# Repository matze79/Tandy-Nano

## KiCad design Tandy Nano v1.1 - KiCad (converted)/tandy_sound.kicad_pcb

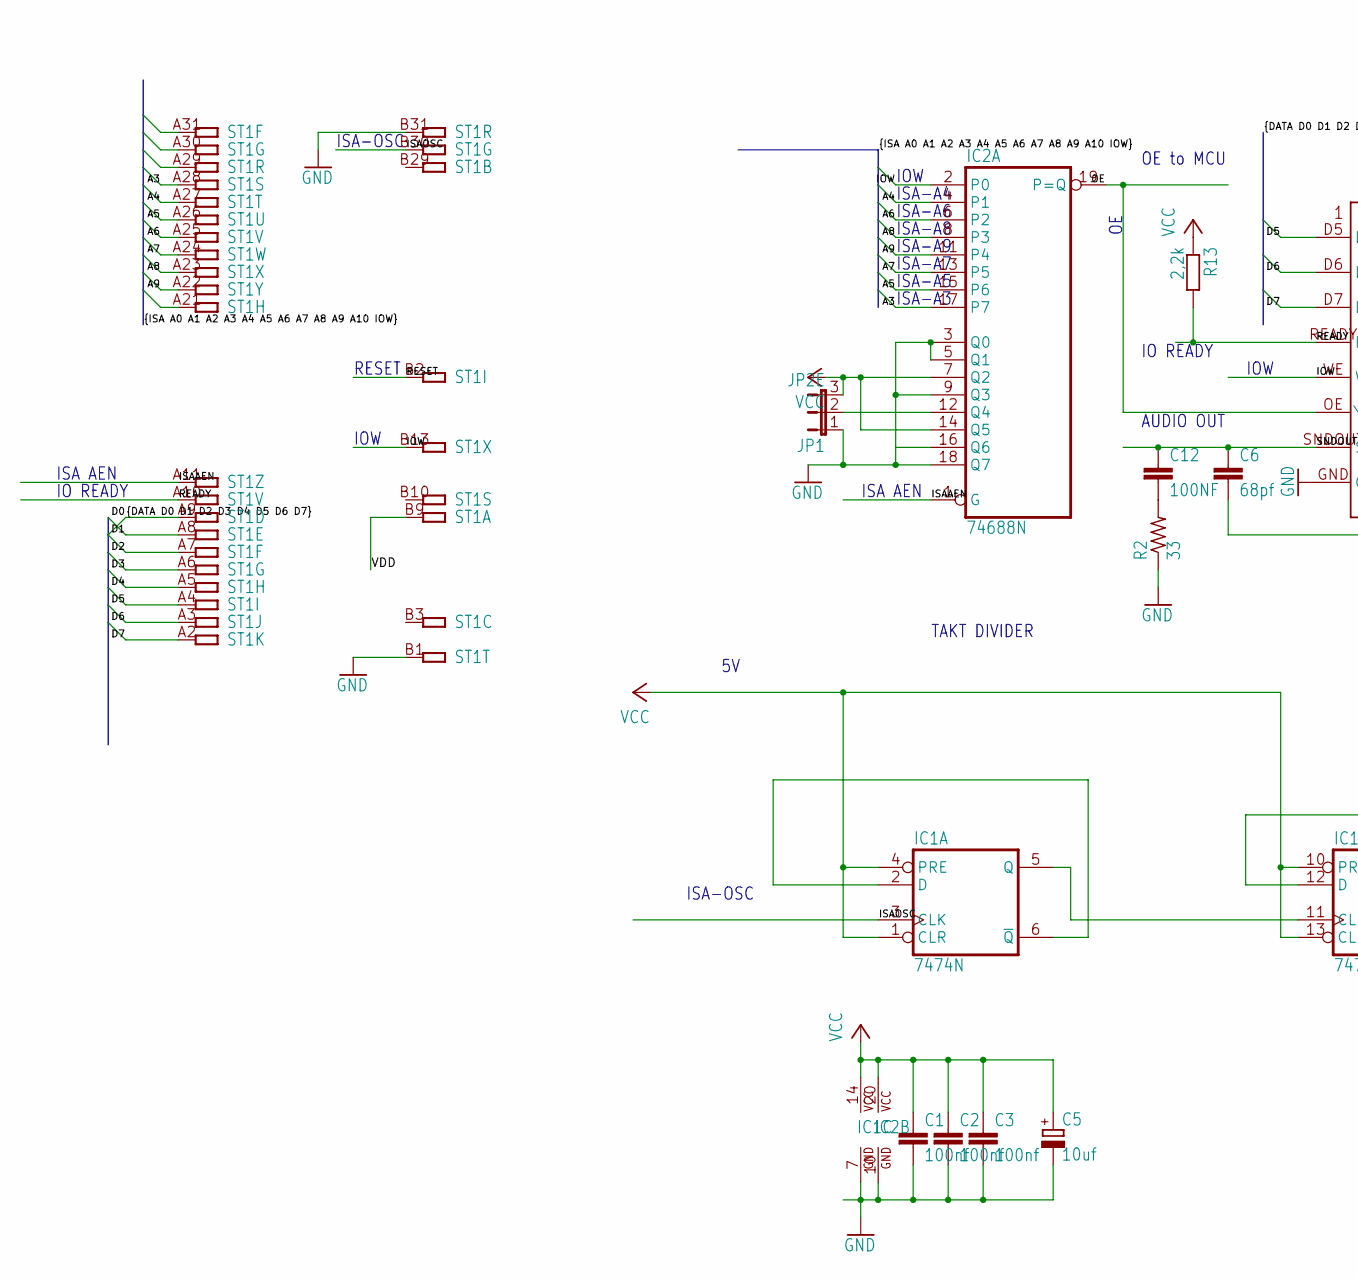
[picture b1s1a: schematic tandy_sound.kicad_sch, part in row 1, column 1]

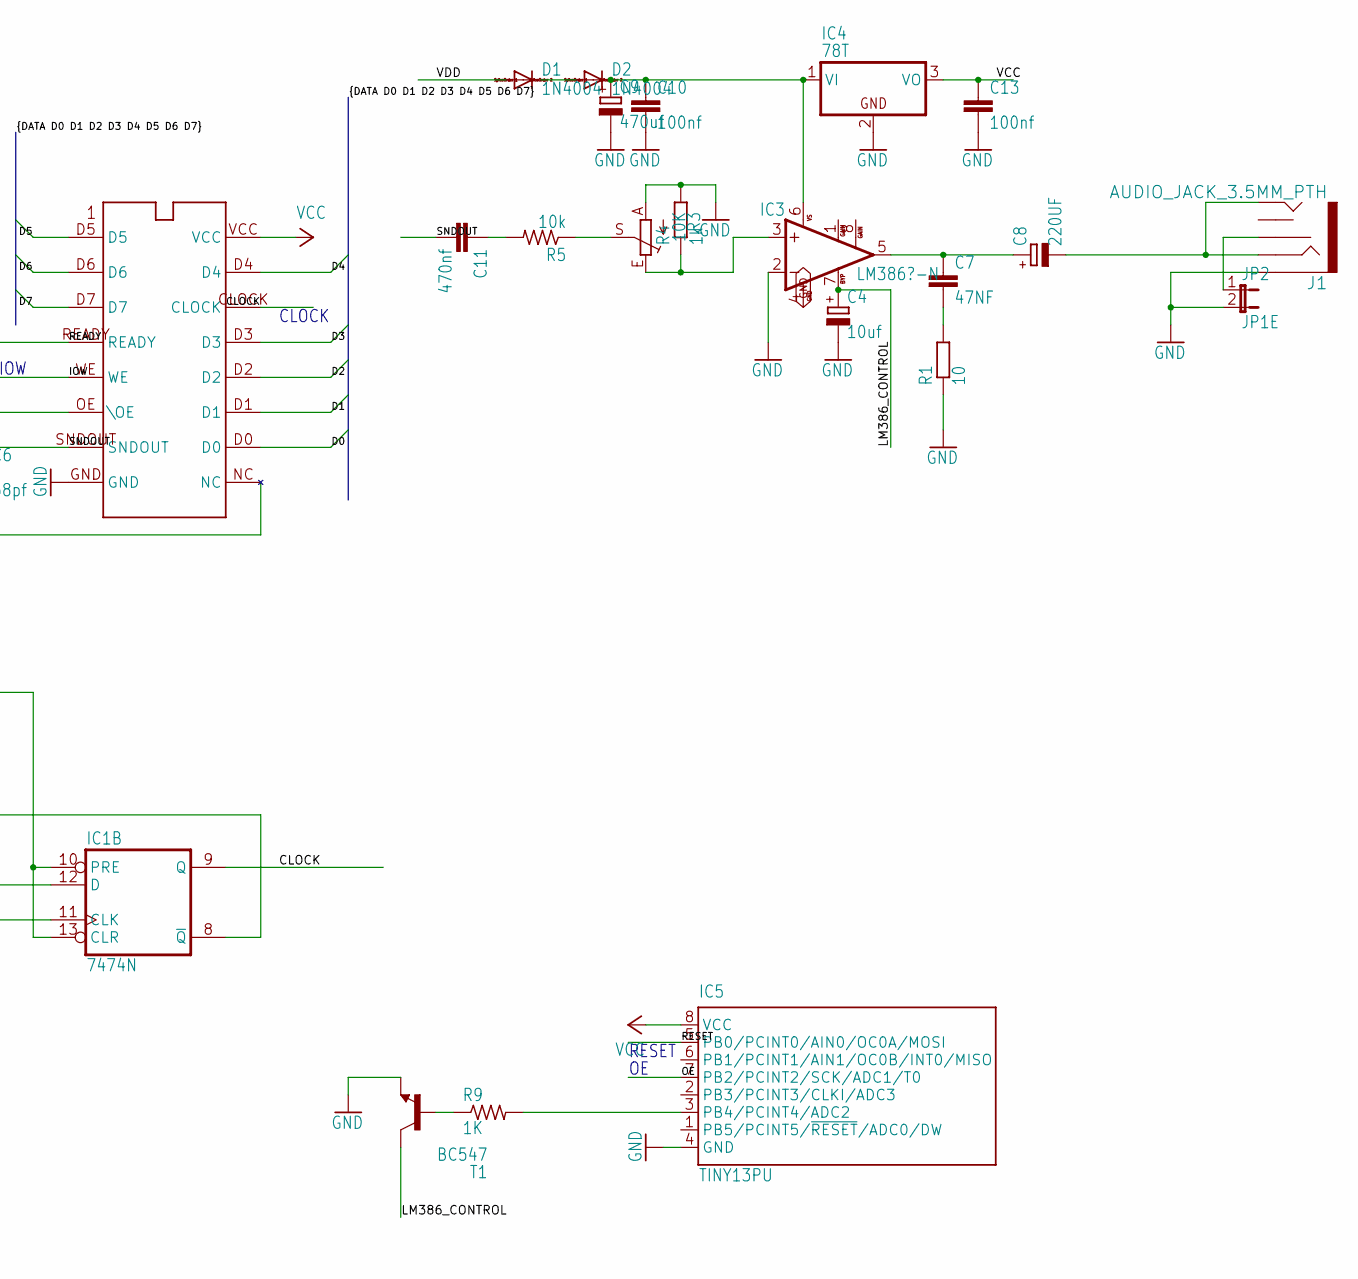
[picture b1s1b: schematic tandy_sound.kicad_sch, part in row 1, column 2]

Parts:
C1, C2, C3, C10, C13: 100nf; C2.5-3
C4, C5: 10uf; E2,5-6
C6: 68pf; C025-030X050
C7: 47NF; C025-030X050
C8: 220UF; E2,5-6E
C9: 470uf; E2,5-6
C11: 470nf; C025-030X050
C12: 100NF; C025-030X050
D1, D2: 1N4004; DO41-10
IC1: 7474N; DIL14
IC2: 74688N; DIL20
IC3: LM386?-N; DIL08
IC4: 78T; TO220H
IC5: TINY13PU; DIL08
J1: AUDIO_JACK_3.5MM_PTH; AUDIO-JACK
JP1: JP2E; JP2
JP2: JP1E; JP1
R1: 10; 0207_10
R2: 33; 0204V
R3: 10K; PT-10S
R4: 1k; 0207_10
R5: 10k; 0204V
R9: 1K; 0204V
R13: 2,2k; 0207_10
ST1: IBM8BIT
T1: BC547; TO92
U$1: SN76489; DIL16

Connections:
A0: ST1.A31
A1: ST1.A30
A2: ST1.A29
A3: IC2.17 (P7), ST1.A28
A4: IC2.4 (P1), ST1.A27
A5: IC2.15 (P6), ST1.A26
A6: IC2.6 (P2), ST1.A25
A7: IC2.13 (P5), ST1.A24
A8: IC2.8 (P3), ST1.A23
A9: IC2.11 (P4), ST1.A22
A10: ST1.A21
CLOCK: IC1.9 (Q), U$1.CLOCK
CMS_CLOCK: IC1.5 (Q), IC1.11 (CLK)
D0: ST1.A9, U$1.D0
D1: ST1.A8, U$1.D1
D2: ST1.A7, U$1.D2
D3: ST1.A6, U$1.D3
D4: ST1.A5, U$1.D4
D5: ST1.A4, U$1.D5
D6: ST1.A3, U$1.D6
D7: ST1.A2, U$1.D7
GND: C1.2, C2.2, C3.2, C4.-, C5.-, C9.-, C10.2, C13.2, IC1.7 (GND), IC2.3 (Q0), IC2.5 (Q1), IC2.9 (Q3), IC2.10 (GND), IC2.16 (Q6), IC2.18 (Q7), IC3.2 (-IN), IC3.4 (GND), IC4.2 (GND), IC5.4 (GND), J1.SLEEVE, JP1.1, JP2.2, R1.1, R2.1, R3.A, R4.2, ST1.B1, ST1.B31, T1.1 (E), U$1.GND
IOW: IC2.2 (P0), ST1.B13, U$1.WE
ISAAEN: IC2.1 (G), ST1.A11
ISAOSC: IC1.3 (CLK), ST1.B30
LM386_CONTROL: C4.+, IC3.7 (BYPASS), T1.3 (C)
unnamed: C8.-, J1.RING, J1.TIP
unnamed: IC1.2 (D), IC1.6 (~Q)
unnamed: C6.2, U$1.NC
unnamed: IC5.3 (PB4/PCINT4/ADC2), R9.2
unnamed: IC1.8 (~Q), IC1.12 (D)
unnamed: C7.2, R1.2
unnamed: D1.C, D2.A
unnamed: IC2.12 (Q4), JP1.2
unnamed: C7.1, C8.+, IC3.5 (OUT)
unnamed: C9.+, C10.1, D2.C, IC3.6 (VS), IC4.1 (VI)
unnamed: IC3.3 (+IN), R3.E, R4.1
unnamed: R3.S, R5.1
unnamed: R9.1, T1.2 (B)
unnamed: C12.2, R2.2
unnamed: C11.1, R5.2
unnamed: J1.RSH, JP2.1
OE: IC2.19 (P=Q), IC5.7 (PB2/PCINT2/SCK/ADC1/T0), U$1.OE (\OE)
READY: R13.2, ST1.A10, U$1.READY
RESET: IC5.5 (PB0/PCINT0/AIN0/OC0A/MOSI), ST1.B2
SNDOUT: C6.1, C11.2, C12.1, U$1.SNDOUT
VCC: C1.1, C2.1, C3.1, C5.+, C13.1, IC1.1 (CLR), IC1.4 (PRE), IC1.10 (PRE), IC1.13 (CLR), IC1.14 (VCC), IC2.7 (Q2), IC2.14 (Q5), IC2.20 (VCC), IC4.3 (VO), IC5.8 (VCC), JP1.3, R13.1, U$1.VCC
VDD: D1.A, ST1.B9

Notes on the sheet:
ISA-OSC
IOW
ISA-A4
RESET
TAKT DIVIDER
IO READY
ISA-A6
ISA-A9
ISA AEN
OE to MCU
AUDIO OUT
CLOCK
ISA-A8
ISA-A7
ISA-A3
ISA-A5

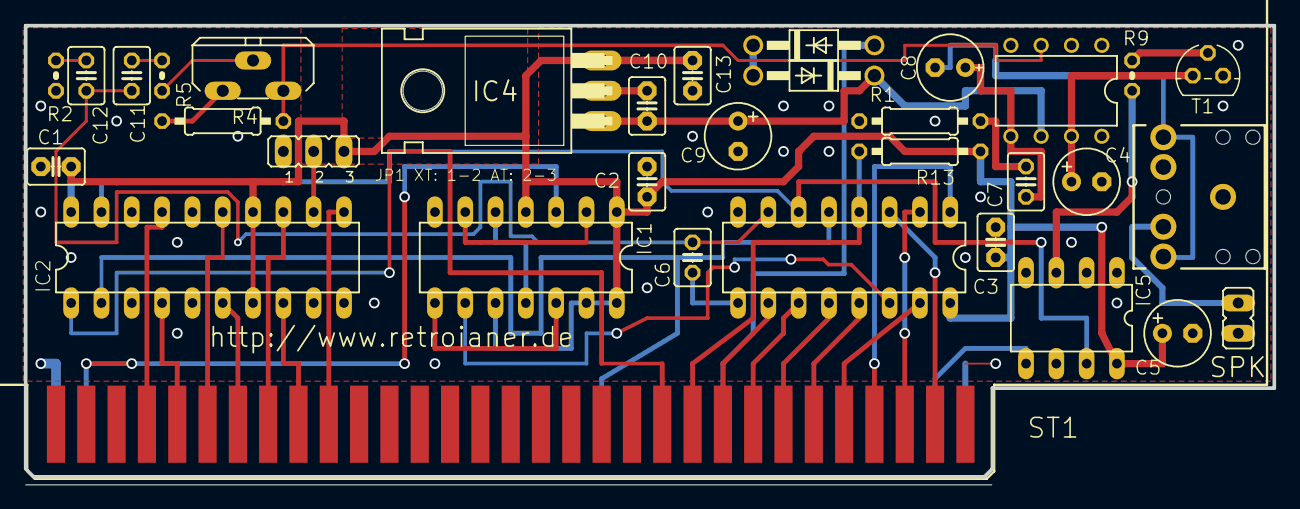
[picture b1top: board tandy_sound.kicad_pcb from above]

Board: 2 copper layers, 104.6 x 38.3 mm, 33 parts (0 on the bottom side), 44 nets.

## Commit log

2025-11-23 Add GNU General Public License v2
2025-11-29 clean up
2025-11-30 Firmware added
2025-11-30 Kicad Files
